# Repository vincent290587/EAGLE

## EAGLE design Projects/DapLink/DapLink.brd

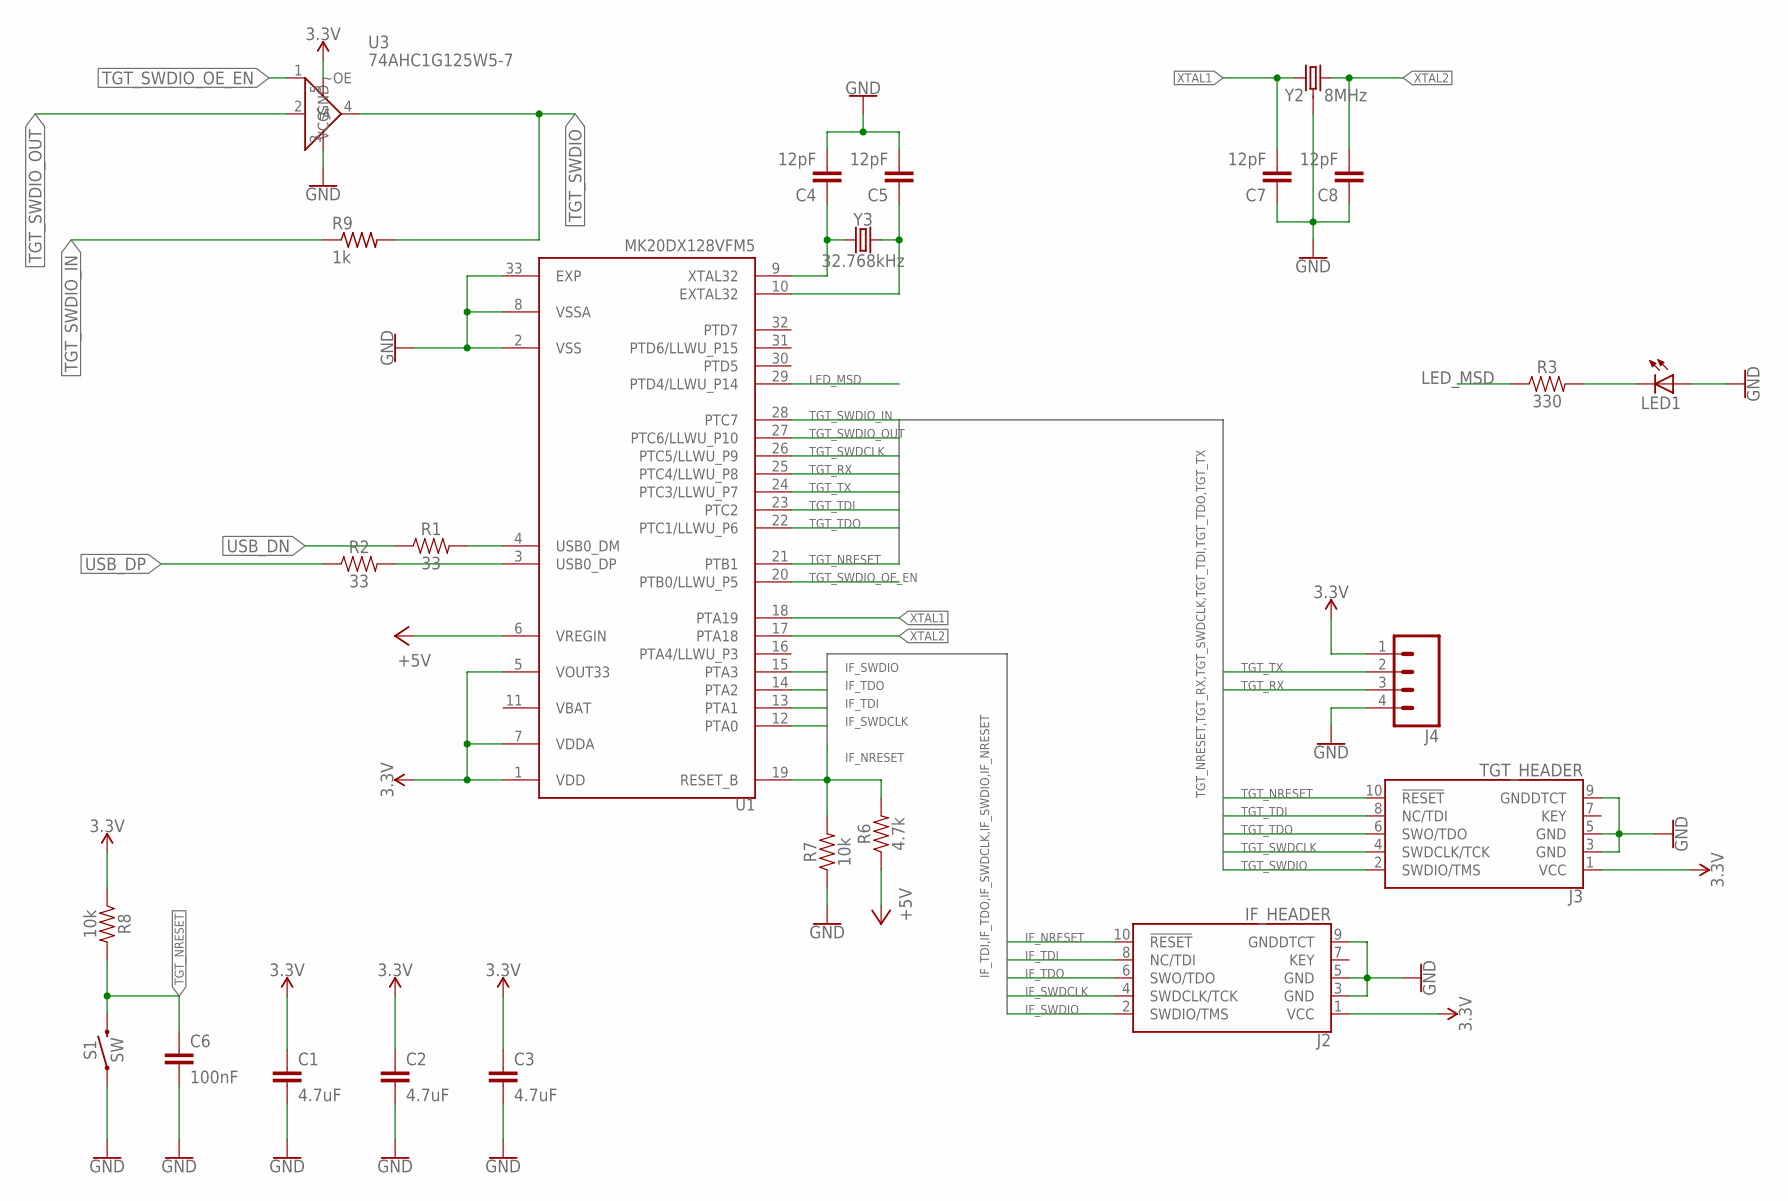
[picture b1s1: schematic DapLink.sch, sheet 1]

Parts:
C1, C2, C3: 4.7uF; 0603
C4, C5, C7, C8: 12pF; 0603
C6: 100nF; 0603
J2: IF_HEADER; 2X5-PTH-1.27MM
J3: TGT_HEADER; 2X5-PTH-1.27MM
J4: CONN_04; 1X04
LED1: LEDCHIP-LED0603; CHIP-LED0603
R1, R2: 33; 0603
R3: 330; 0603
R6: 4.7k; 0603
R7, R8: 10k; 0603
R9: 1k; R0603
S1: SW; TACTILE_SWITCH_PTH_6.0MM_KIT
U1: MK20DX128VFM5; QFN50P500X500X100-33N
U3: 74AHC1G125W5-7; SOT95P280X140-5N
Y2: 8MHz; CRYSTAL-SMD-5X3.2-4PAD
Y3: 32.768kHz; CRYSTAL-SMD-3.2X1.5MM

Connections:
3.3V: C1.1, C2.1, C3.1, J2.1 (VCC), J3.1 (VCC), J4.1, R8.1, U1.1 (VDD), U1.5 (VOUT33), U1.7 (VDDA), U3.5 (VCC); also elsewhere on the board
+5V: R6.1, U1.6 (VREGIN); also elsewhere on the board
GND: C1.2, C2.2, C3.2, C4.2, C5.2, C6.2, C7.1, C8.1, J2.3 (GND), J2.5 (GND), J2.9 (GNDDTCT), J3.3 (GND), J3.5 (GND), J3.9 (GNDDTCT), J4.4, LED1.A, R7.1, S1.1, U1.2 (VSS), U1.8 (VSSA), U1.33 (EXP), U3.3 (GND), Y2.2 (3), Y2.4 (3); also elsewhere on the board
IF_NRESET: J2.10 (!RESET), R6.2, R7.2, U1.19 (RESET_B)
IF_SWDCLK: J2.4 (SWDCLK/TCK), U1.12 (PTA0)
IF_SWDIO: J2.2 (SWDIO/TMS), U1.15 (PTA3)
IF_TDI: J2.8 (NC/TDI), U1.13 (PTA1)
IF_TDO: J2.6 (SWO/TDO), U1.14 (PTA2)
LED_MSD: R3.1, U1.29 (PTD4/LLWU_P14)
unnamed: C4.1, U1.9 (XTAL32), Y3.P$1 (1)
unnamed: C5.1, U1.10 (EXTAL32), Y3.P$2 (2)
unnamed: LED1.C, R3.2
TGT_NRESET: C6.1, J3.10 (!RESET), R8.2, S1.3 (2), U1.21 (PTB1)
TGT_RX: J4.3, U1.25 (PTC4/LLWU_P8)
TGT_SWDCLK: J3.4 (SWDCLK/TCK), U1.26 (PTC5/LLWU_P9)
TGT_SWDIO: J3.2 (SWDIO/TMS), R9.2, U3.4 (Y)
TGT_SWDIO_IN: R9.1, U1.28 (PTC7)
TGT_SWDIO_OE_EN: U1.20 (PTB0/LLWU_P5), U3.1 (~OE)
TGT_SWDIO_OUT: U1.27 (PTC6/LLWU_P10), U3.2 (A)
TGT_TDI: J3.8 (NC/TDI), U1.23 (PTC2)
TGT_TDO: J3.6 (SWO/TDO), U1.22 (PTC1/LLWU_P6)
TGT_TX: J4.2, U1.24 (PTC3/LLWU_P7)
USB0_DN: R1.2, U1.4 (USB0_DM)
USB0_DP: R2.2, U1.3 (USB0_DP)
USB_DN: R1.1; also elsewhere on the board
USB_DP: R2.1; also elsewhere on the board
VBAT: U1.11 (VBAT)
XTAL1: C7.2, U1.18 (PTA19), Y2.3 (1)
XTAL2: C8.2, U1.17 (PTA18), Y2.1 (2)

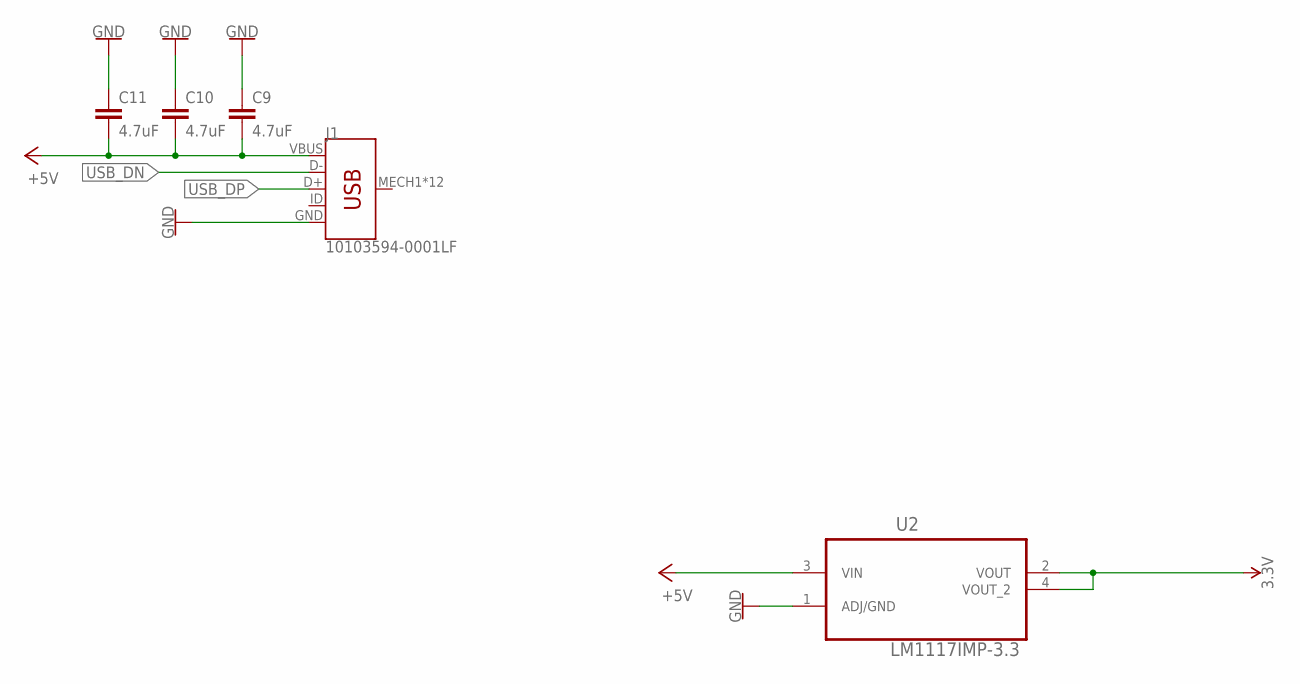
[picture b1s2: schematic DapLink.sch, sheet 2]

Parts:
C9, C10, C11: 4.7uF; C0603
J1: 10103594-0001LF
U2: LM1117IMP-3.3; SOT230P696X180-4N

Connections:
3.3V: U2.2 (VOUT), U2.4 (VOUT_2); also elsewhere on the board
+5V: C9.2, C10.2, C11.2, J1.VBUS, U2.3 (VIN); also elsewhere on the board
GND: C9.1, C10.1, C11.1, J1.GND, U2.1 (ADJ/GND); also elsewhere on the board
USB_DN: J1.D-; also elsewhere on the board
USB_DP: J1.D+; also elsewhere on the board

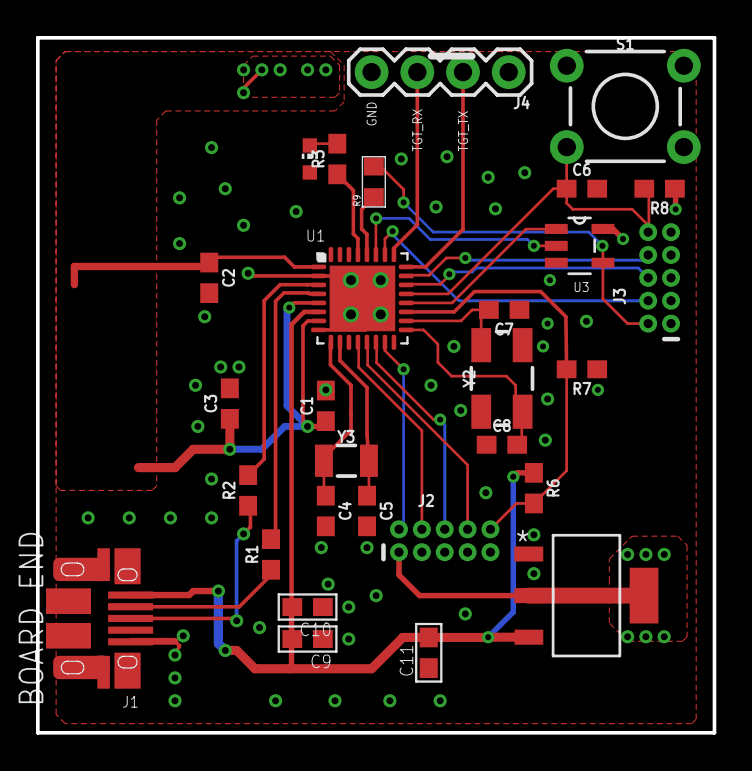
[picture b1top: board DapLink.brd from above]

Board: 2 copper layers, 37.6 x 38.6 mm, 29 parts (0 on the bottom side), 28 nets.

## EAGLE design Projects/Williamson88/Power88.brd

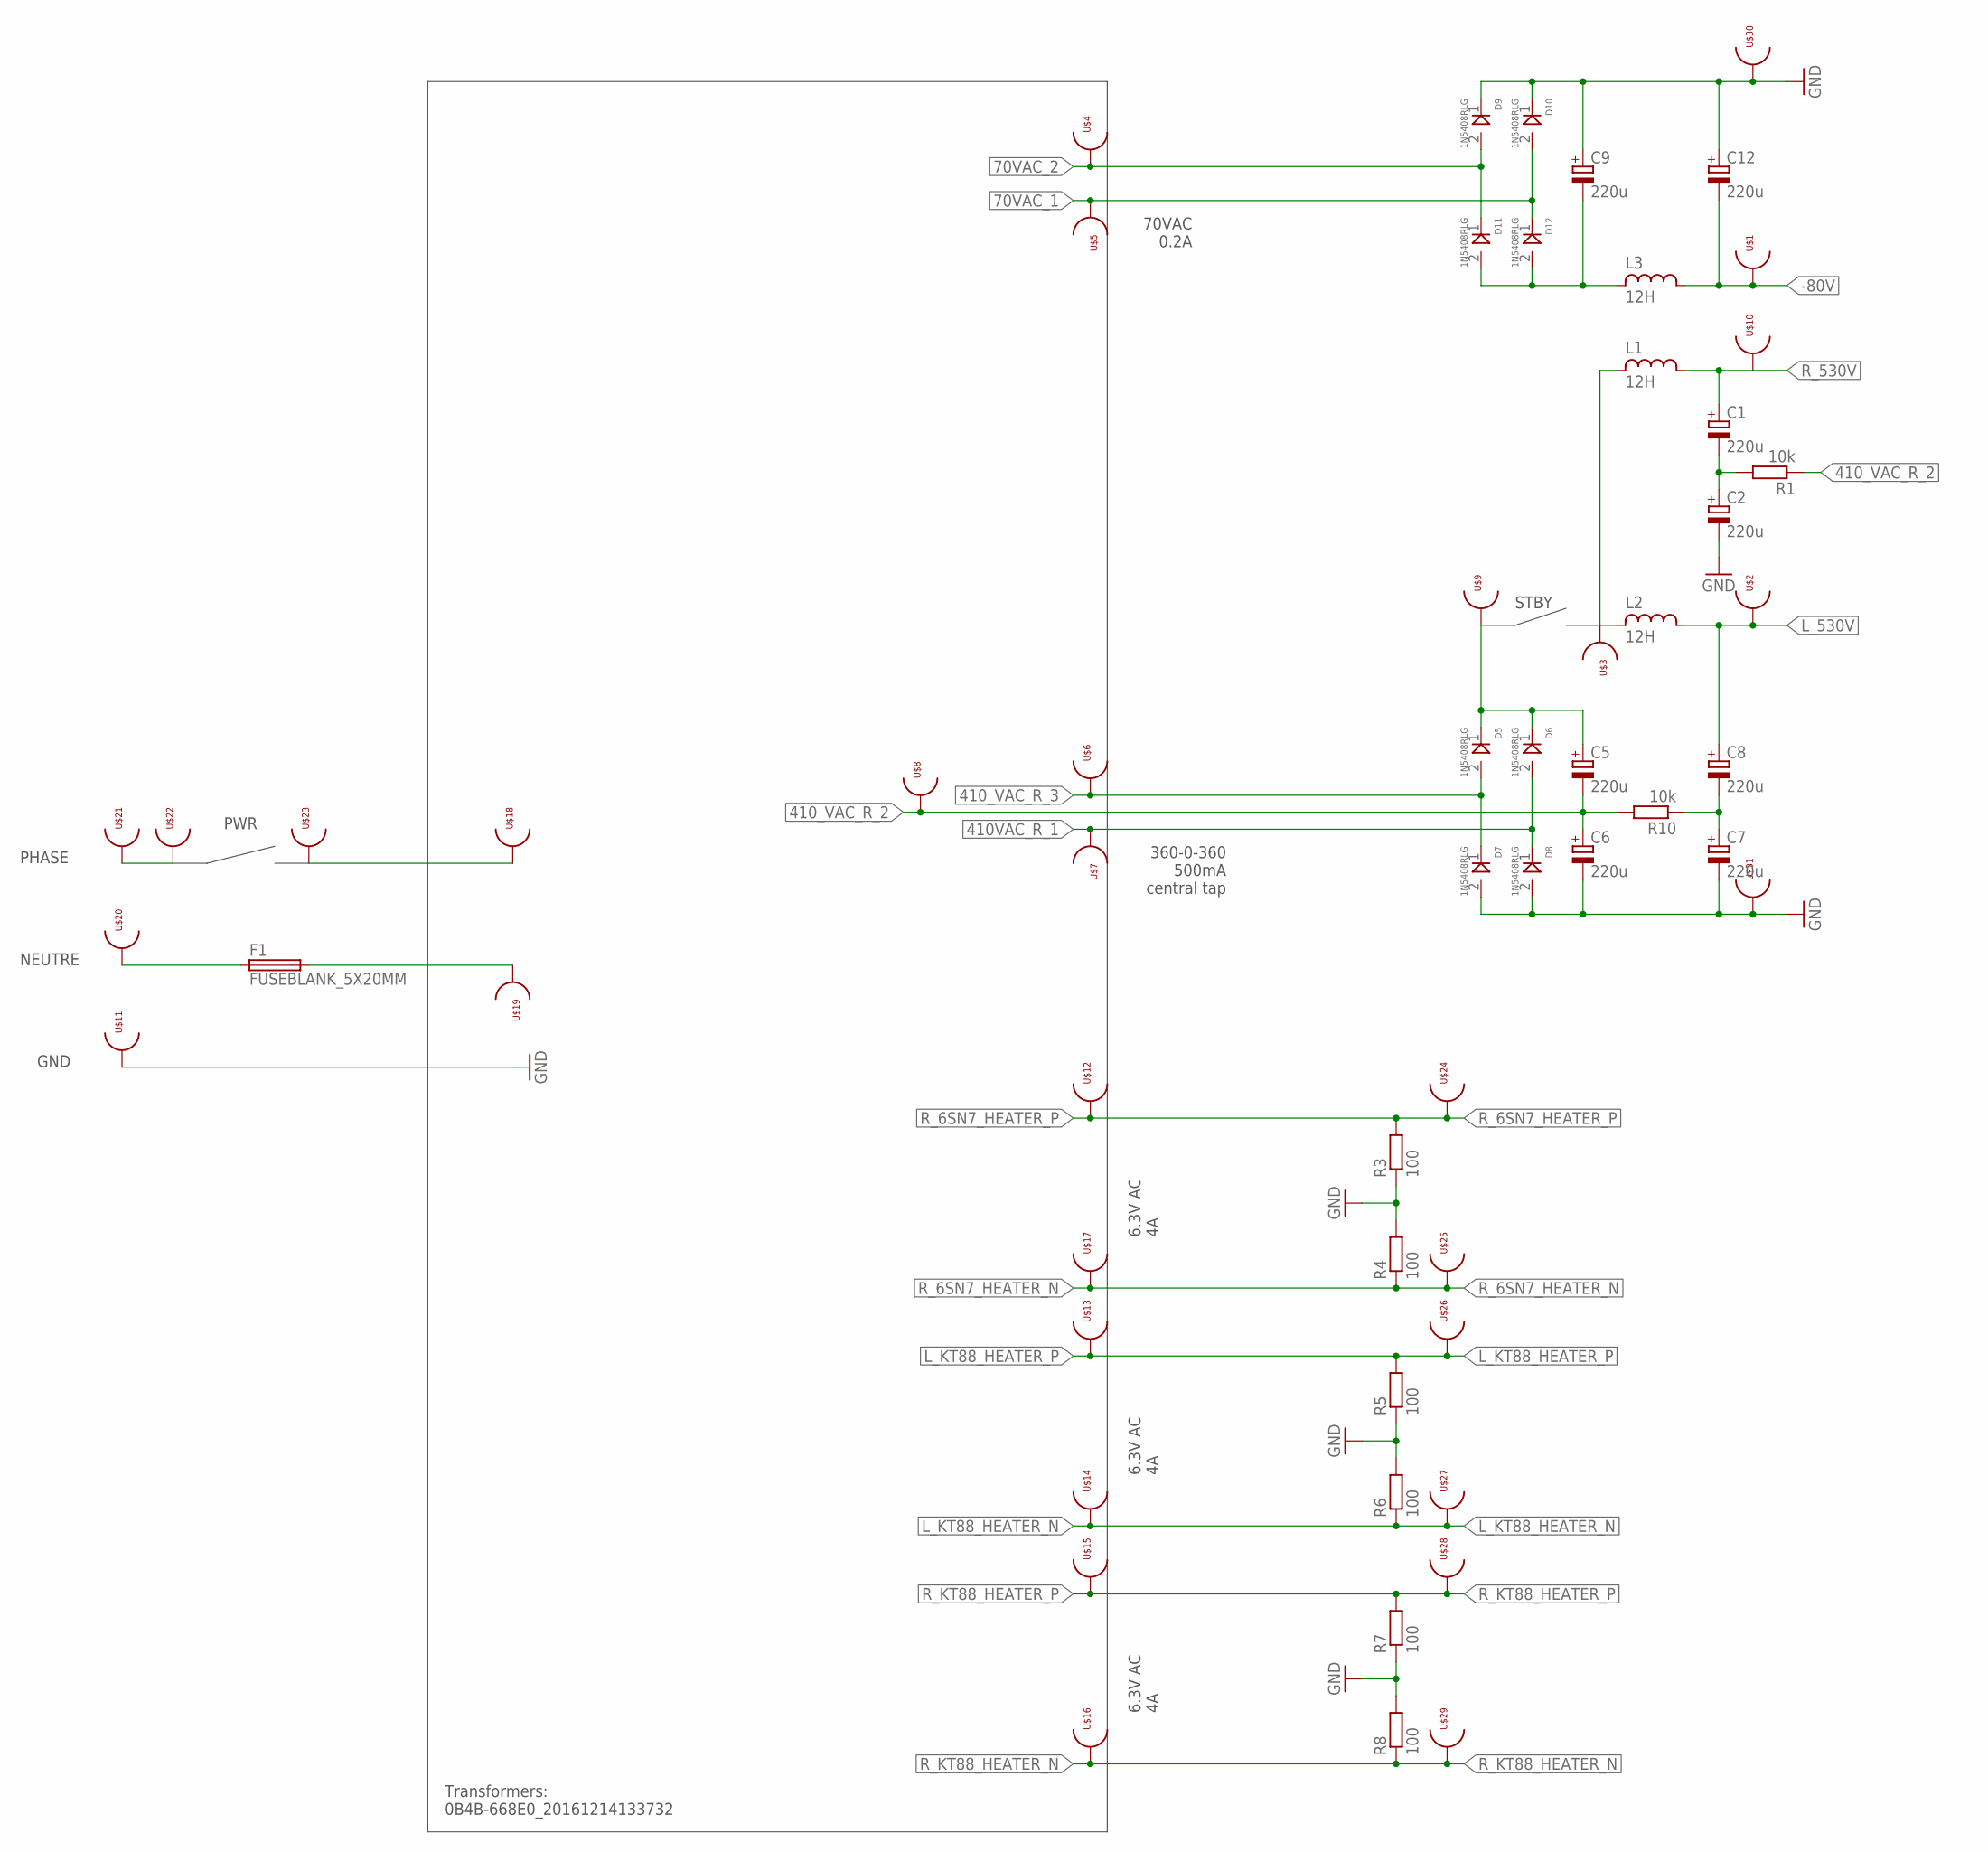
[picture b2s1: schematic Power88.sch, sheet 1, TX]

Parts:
C1, C2, C5, C6, C7, C8, C9, C12: 220u; E7,5-16; RATING 300V
D5, D6, D7, D8, D9, D10, D11, D12: 1N5408RLG; DIOAD2860W130L840D505
F1: FUSEBLANK_5X20MM; FUSE_HOLDER_5X20MM
L1, L2, L3: 12H; RL622; RATING 200mA
R1, R10: 10k; R1206
R3, R4, R5, R6, R7, R8: 100; R1206
U$1, U$2, U$3, U$4, U$5, U$6, U$7, U$8, U$9, U$10, U$11, U$12, U$13, U$14, U$15, U$16, U$17, U$18, U$19, U$20, U$21, U$22, U$23, U$24, U$25, U$26, U$27, U$28, U$29, U$30, U$31: TESTPOINT_HOLE; TESTPOINT_PHOLE

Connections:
70VAC_1: D10.2 (A), D12.1 (K), U$5.P$1
70VAC_2: D9.2 (A), D11.1 (K), U$4.P$1
410VAC_R_1: D6.2 (A), D8.1 (K), U$7.P$1
410_VAC_R_2: C5.-, C6.+, R1.1, R10.2, U$8.P$1
410_VAC_R_3: D5.2 (A), D7.1 (K), U$6.P$1
530V: C5.+, D5.1 (K), D6.1 (K), U$9.P$1
-80V: C12.-, L3.2, U$1.P$1
AC_PLUG_N: F1.1, U$20.P$1
AC_PLUG_PHASE: U$21.P$1, U$22.P$1
GND: C2.-, C6.-, C7.-, C9.+, C12.+, D7.2 (A), D8.2 (A), D9.1 (K), D10.1 (K), R3.1, R4.2, R5.1, R6.2, R7.1, R8.2, U$11.P$1, U$30.P$1, U$31.P$1
L_530V: C8.+, L2.2, U$2.P$1
L_KT88_HEATER_N: R6.1, U$14.P$1, U$27.P$1
L_KT88_HEATER_P: R5.2, U$13.P$1, U$26.P$1
unnamed: C7.+, C8.-, R10.1
unnamed: L1.1, L2.1, U$3.P$1
unnamed: C1.-, C2.+, R1.2
unnamed: F1.2, U$19.P$1
unnamed: C9.-, D11.2 (A), D12.2 (A), L3.1
R_6SN7_HEATER_N: R4.1, U$17.P$1, U$25.P$1
R_6SN7_HEATER_P: R3.2, U$12.P$1, U$24.P$1
R_530V: C1.+, L1.2, U$10.P$1
R_KT88_HEATER_N: R8.1, U$16.P$1, U$29.P$1
R_KT88_HEATER_P: R7.2, U$15.P$1, U$28.P$1
SW_ACIN: U$18.P$1, U$23.P$1

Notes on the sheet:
6.3V AC 4A
360-0-360 500mA central tap
70VAC 0.2A
Transformers: 0B4B-668E0_20161214133732
PWR
STBY
GND
NEUTRE
PHASE

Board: 2 copper layers, 59 parts (0 on the bottom side), 24 nets, no tracks yet.

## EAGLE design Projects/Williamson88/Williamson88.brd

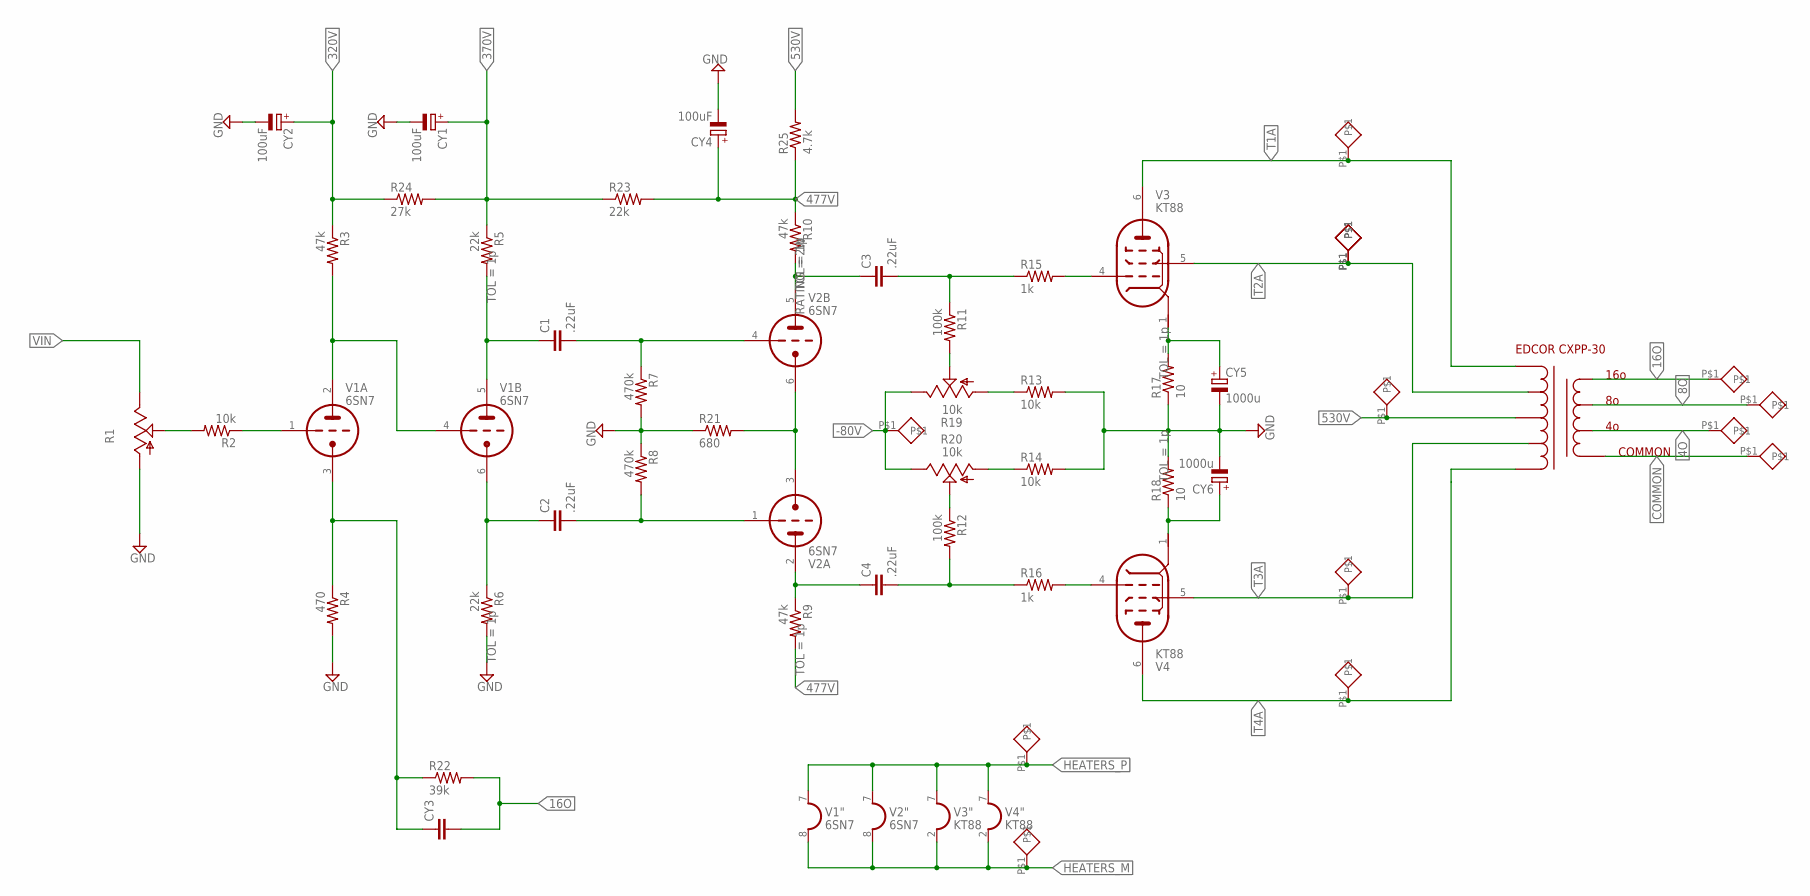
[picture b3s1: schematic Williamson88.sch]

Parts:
C1, C2, C3, C4: .22uF; C225-062X268; MPN 150224J630LE
CY1, CY2, CY4: 100uF; E7,5-18; RATING 600V
CY3: CYYC10B5; YC10B5
CY5, CY6: 1000u; E7,5-18; RATING 50V
R1: TRIM_US-B25P; B25P
R2, R13, R14: 10k; 0309/10
R3: 47k; 0309/10
R4: 470; 0309/10
R5, R6, R23: 22k; 0309/10
R7, R8: 470k; 0309/10
R9, R10: 47k; 0309/10; RATING 2W
R11, R12: 100k; 0309/10
R15, R16: 1k; 0309/10
R17, R18: 10; 0309/10; RATING 5W
R19, R20: 10k; B25P
R21: 680; 0309/10
R22: 39k; 0309/10
R24: 27k; 0309/10
R25: 4.7k; 0309/10; RATING 5W
U$1: CXPP30
U$2, U$3, U$4, U$5, U$6, U$7, U$8, U$9, U$10, U$14, U$15, U$17, U$18: W_CONN; WIRE_T
V1, V2: 6SN7; OKTAL
V3, V4: KT88; OKTAL

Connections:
4O: U$8.P$1
8O: U$7.P$1
16O: CY3.2, R22.2, U$6.P$1
320V: CY2.+, R3.1, R24.1
370V: CY1.+, R5.1, R23.1, R24.2
477V: CY4.+, R9.2, R10.1, R23.2, R25.1
530V: R25.2, U$18.P$1
-80V: R19.E, R20.E, U$10.P$1
COMMON: U$9.P$1
GND: CY1.-, CY2.-, CY4.-, CY5.-, CY6.-, R1.A, R4.2, R6.2, R7.2, R8.1, R13.2, R14.2, R17.1, R18.2, R21.1
HEATERS_M: U$15.P$1, V1.8 (H2), V2.8 (H2), V3.2 (H2), V4.2 (H2)
HEATERS_P: U$14.P$1, V1.7 (H1), V2.7 (H1), V3.7 (H1), V4.7 (H1)
unnamed: R3.2, V1.2 (TA), V1.4 (TG)
unnamed: CY3.1, R4.1, R22.1, V1.3 (TK)
unnamed: C2.1, R6.1, V1.6 (TK)
unnamed: C1.1, R5.2, V1.5 (TA)
unnamed: C1.2, R7.1, V2.4 (TG)
unnamed: C2.2, R8.2, V2.1 (TG)
unnamed: R1.S, R2.2
unnamed: R21.2, V2.3 (TK), V2.6 (TK)
unnamed: C3.1, R10.2, V2.5 (TA)
unnamed: C4.1, R9.1, V2.2 (TA)
unnamed: C3.2, R11.1, R15.1
unnamed: R15.2, V3.4 (PG)
unnamed: C4.2, R12.2, R16.1
unnamed: R16.2, V4.4 (PG)
unnamed: CY5.+, R17.2, V3.1 (PK)
unnamed: CY6.+, R18.1, V4.1 (PK)
unnamed: R13.1, R19.A
unnamed: R2.1, V1.1 (TG)
unnamed: R14.1, R20.A
unnamed: R12.1, R20.S
unnamed: R11.2, R19.S
T1A: U$2.P$1, V3.6 (PA)
T2A: U$3.P$1, U$17.P$1, V3.5 (PSG)
T3A: U$4.P$1, V4.5 (PSG)
T4A: U$5.P$1, V4.6 (PA)
VIN: R1.E

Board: 2 copper layers, 53 parts (0 on the bottom side), 34 nets, no tracks yet.

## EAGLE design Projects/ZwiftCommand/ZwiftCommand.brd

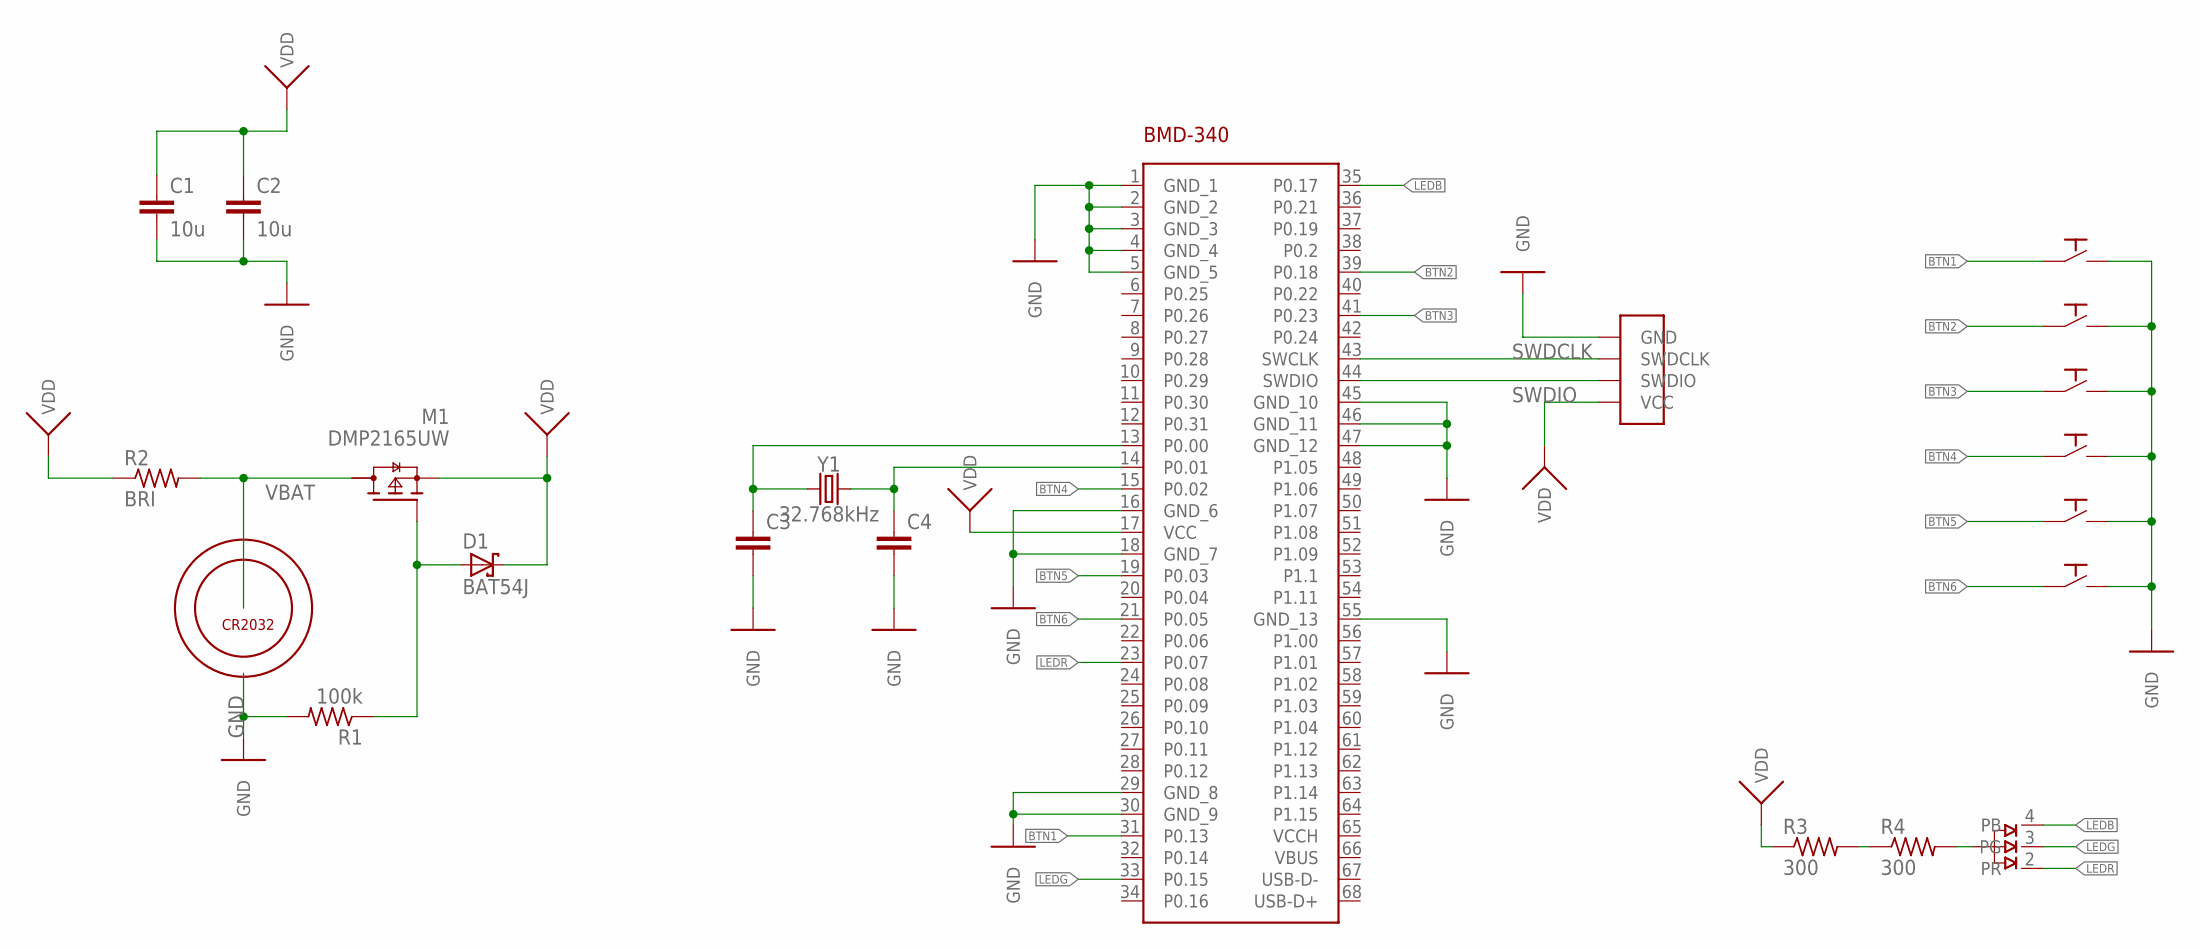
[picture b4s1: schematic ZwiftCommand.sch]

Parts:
C1, C2: 10u; C0603
C3, C4: C-EUC0603; C0603
D1: BAT54J; SOD323(F)
D2: LRTBR48G; LRTBR48GP9Q71R7S526NP68
IC1: BMD-340-A-R; BMD340AR
M1: DMP2165UW; SOT65P210X110-3N
R1: 100k; R0603
R2: BRI; R0402
R3, R4: 300; R0603
SPST1, SPST2, SPST3, SPST4, SPST5, SPST6: PTS526SK08; PTS526SKG15SMTR2LFS
U1: BAT-HLD-001-THM; BATHLD001THM
U$2: PROG_SMD
Y1: 32.768kHz; CRYSTAL-SMD-3.2X1.5MM

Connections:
BTN1: IC1.31 (P0.13), SPST1.1, SPST1.2
BTN2: IC1.39 (P0.18), SPST2.1, SPST2.2
BTN3: IC1.41 (P0.23), SPST3.1, SPST3.2
BTN4: IC1.15 (P0.02), SPST4.1, SPST4.2
BTN5: IC1.19 (P0.03), SPST5.1, SPST5.2
BTN6: IC1.21 (P0.05), SPST6.1, SPST6.2
GND: C1.2, C2.2, C3.2, C4.2, IC1.1 (GND_1), IC1.2 (GND_2), IC1.3 (GND_3), IC1.4 (GND_4), IC1.5 (GND_5), IC1.16 (GND_6), IC1.18 (GND_7), IC1.29 (GND_8), IC1.30 (GND_9), IC1.45 (GND_10), IC1.46 (GND_11), IC1.47 (GND_12), IC1.55 (GND_13), R1.2, SPST1.3, SPST1.4, SPST2.3, SPST2.4, SPST3.3, SPST3.4, SPST4.3, SPST4.4, SPST5.3, SPST5.4, SPST6.3, SPST6.4, U1.5 (-), U$2.GND
LEDB: D2.4 (PB), IC1.35 (P0.17)
LEDG: D2.3 (PG), IC1.33 (P0.15)
LEDR: D2.2 (PR), IC1.23 (P0.07)
unnamed: C3.1, IC1.13 (P0.00), Y1.P$1 (1)
unnamed: D1.2 (A), M1.1 (G), R1.1
unnamed: R3.2, R4.1
unnamed: C4.1, IC1.14 (P0.01), Y1.P$2 (2)
unnamed: D2.1, R4.2
SWDCLK: IC1.43 (SWCLK), U$2.PIN1 (SWDCLK)
SWDIO: IC1.44 (SWDIO), U$2.PIN2 (SWDIO)
VBAT: M1.3 (D), R2.2, U1.1 (+), U1.2 (+), U1.3 (+), U1.4 (+)
VDD: C1.1, C2.1, D1.1 (K), IC1.17 (VCC), M1.2 (S), R2.1, R3.1, U$2.VCC

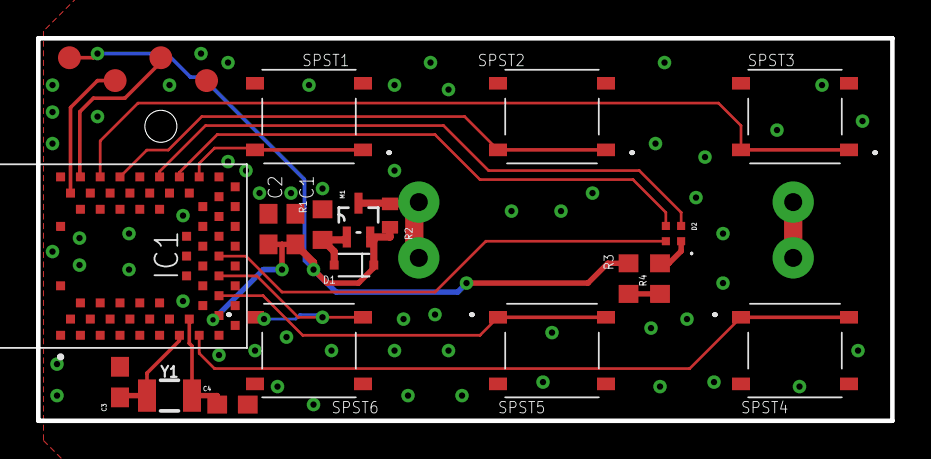
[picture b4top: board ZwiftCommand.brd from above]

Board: 2 copper layers, 47.4 x 21.2 mm, 21 parts (1 on the bottom side), 19 nets.

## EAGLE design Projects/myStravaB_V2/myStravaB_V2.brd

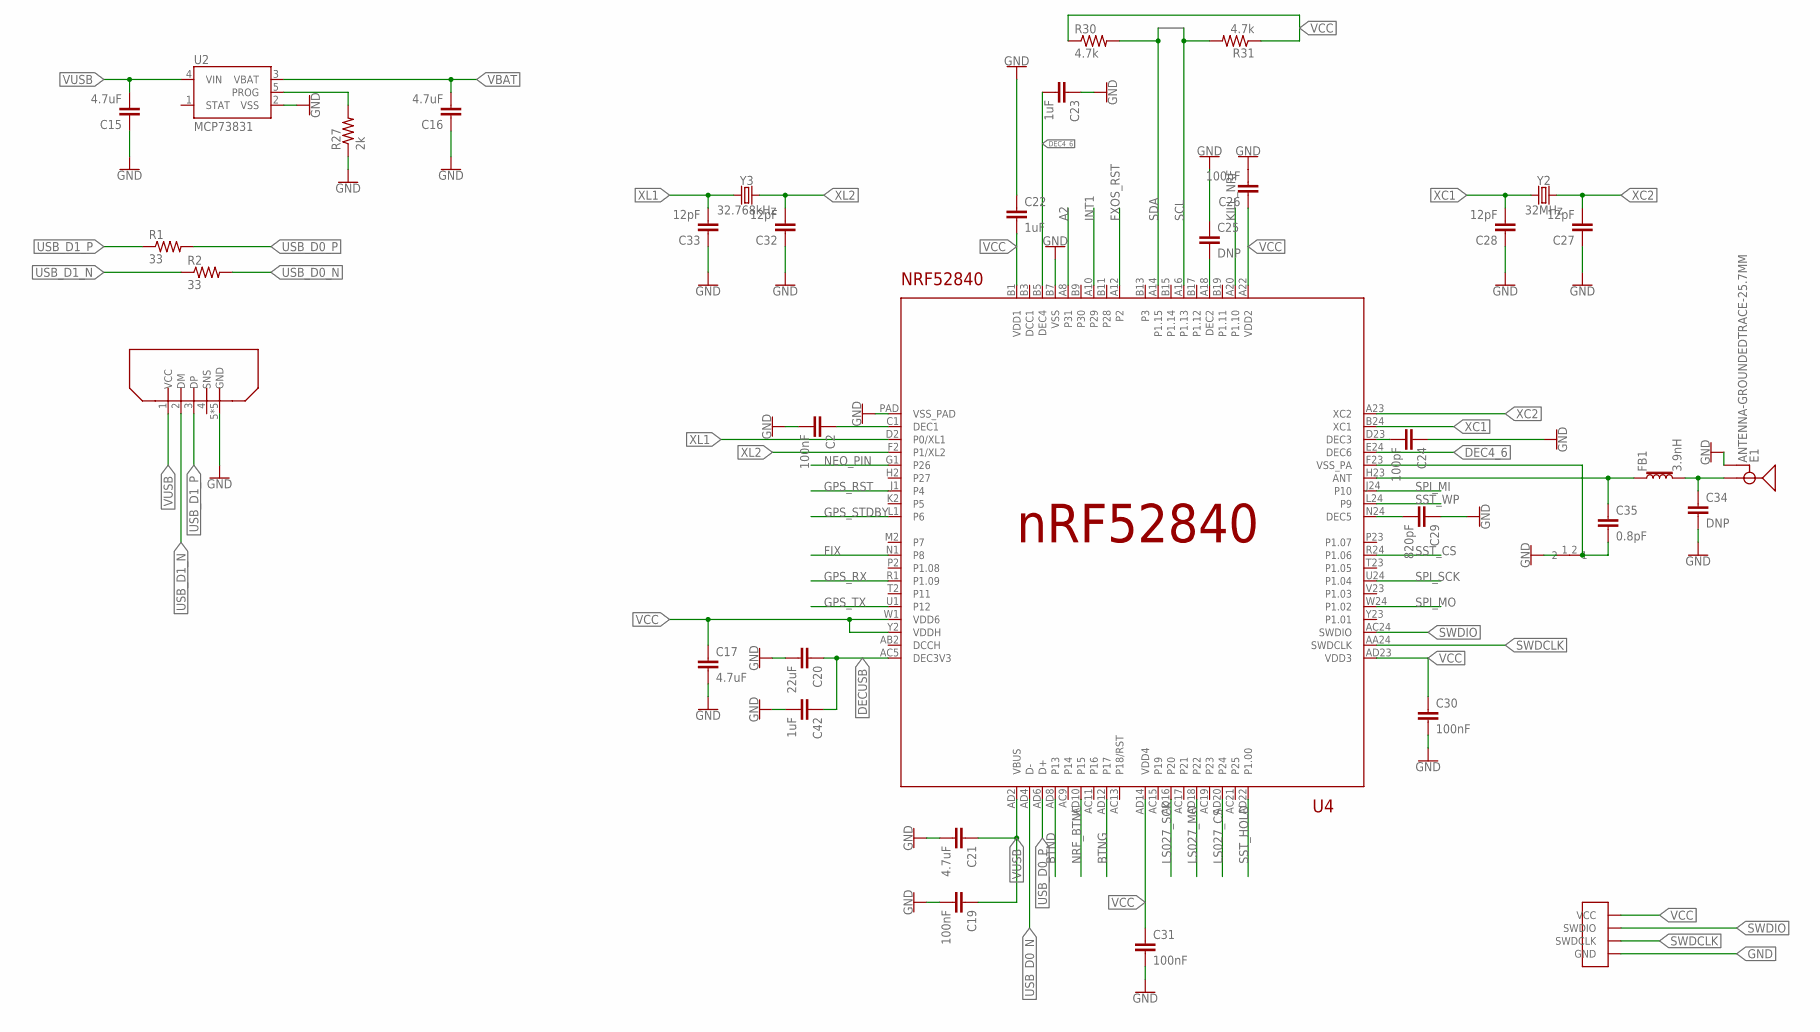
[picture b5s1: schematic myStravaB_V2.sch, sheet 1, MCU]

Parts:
C2, C19, C26: 100nF; C0603
C15, C16, C21: 4.7uF; C0805
C17: 4.7uF; C0603
C20: 22uF; C0603
C22, C23: 1uF; 0603
C24: 100pF; C0603
C25: DNP; C0402
C27, C28: 12pF; C0402
C29: 820pF; C0603
C30, C31: 100nF; C0402
C32, C33: 12pF; C0603
C34: DNP; 0603
C35: 0.8pF; C0402
C42: 1uF; C0603
E1: ANTENNA-GROUNDEDTRACE-25.7MM; TRACE_ANTENNA_2.4GHZ_25.7MM
FB1: 3.9nH; 0603
R1, R2: 33; R0603
R27: 2k; R0603
R30, R31: 4.7k; R0603
U2: MCP73831; SOT23-5
U4: NRF52840; AQFN73
U$3: ZX80B5P
U$7: PROG_SMD
U$8: NET_CONN
Y2: 32MHz; CRYSTAL-SMD-5X3.2-4PAD
Y3: 32.768kHz; CRYSTAL-SMD-3.2X1.5MM

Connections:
A2: U4.A8 (P31)
BTND: U4.AD8 (P13); also elsewhere on the board
BTNG: U4.AD12 (P17); also elsewhere on the board
DEC1: C2.1, U4.C1 (DEC1)
DEC2: C25.2, U4.A18 (DEC2)
DEC3: C24.2, U4.D23 (DEC3)
DEC4_6: C23.2, U4.B5 (DEC4), U4.E24 (DEC6)
DEC5: C29.2, U4.N24 (DEC5)
DECUSB: C20.1, C42.1, U4.AC5 (DEC3V3)
FIX: U4.N1 (P8); also elsewhere on the board
FXOS_RST: U4.A12 (P2); also elsewhere on the board
GND: C2.2, C15.1, C16.1, C17.2, C19.2, C20.2, C21.2, C22.1, C23.1, C24.1, C25.1, C26.2, C27.1, C28.1, C29.1, C30.2, C31.2, C32.1, C33.1, C34.2, C42.2, E1.GND, E1.GND2 (GND), R27.1, U2.2 (VSS), U4.B7 (VSS), U4.PAD (VSS_PAD), U$3.5 (GND), U$3.GND1 (GND), U$3.GND2 (GND), U$3.GND3 (GND), U$3.GND4 (GND), U$7.GND, U$8.1; also elsewhere on the board
GPS_RST: U4.J1 (P4); also elsewhere on the board
GPS_RX: U4.R1 (P1.09); also elsewhere on the board
GPS_STDBY: U4.L1 (P6); also elsewhere on the board
GPS_TX: U4.U1 (P12); also elsewhere on the board
INT1: U4.A10 (P29); also elsewhere on the board
KILL_NRF: U4.A20 (P1.10); also elsewhere on the board
LS027_CS: U4.AD20 (P24); also elsewhere on the board
LS027_MO: U4.AD18 (P22); also elsewhere on the board
LS027_SCK: U4.AD16 (P20); also elsewhere on the board
unnamed: C35.1, FB1.1, U4.H23 (ANT)
unnamed: C34.1, E1.ANT (SIGNAL), FB1.2
unnamed: C35.2, U4.F23 (VSS_PA), U$8.2
unnamed: R27.2, U2.5 (PROG)
NEO_PIN: U4.G1 (P26); also elsewhere on the board
NRF_BTNC: U4.AD10 (P15); also elsewhere on the board
SCL: R31.2, U4.A16 (P1.13); also elsewhere on the board
SDA: R30.2, U4.A14 (P1.15); also elsewhere on the board
SPI_MI: U4.J24 (P10); also elsewhere on the board
SPI_MO: U4.W24 (P1.02); also elsewhere on the board
SPI_SCK: U4.U24 (P1.04); also elsewhere on the board
SST_CS: U4.R24 (P1.06); also elsewhere on the board
SST_HOLD: U4.AD22 (P1.00); also elsewhere on the board
SST_WP: U4.L24 (P9); also elsewhere on the board
SWDCLK: U4.AA24 (SWDCLK), U$7.PIN1 (SWDCLK)
SWDIO: U4.AC24 (SWDIO), U$7.PIN2 (SWDIO)
USB_D0_N: R2.2, U4.AD4 (D-)
USB_D0_P: R1.2, U4.AD6 (D+)
USB_D1_N: R2.1, U$3.2 (DM)
USB_D1_P: R1.1, U$3.3 (DP)
VBAT: C16.2, U2.3 (VBAT); also elsewhere on the board
VCC: C17.1, C22.2, C26.1, C30.1, C31.1, R30.1, R31.1, U4.A22 (VDD2), U4.AD14 (VDD4), U4.AD23 (VDD3), U4.B1 (VDD1), U4.W1 (VDD6), U4.Y2 (VDDH), U$7.VCC; also elsewhere on the board
VUSB: C15.2, C19.1, C21.1, U2.4 (VIN), U4.AD2 (VBUS), U$3.1 (VCC); also elsewhere on the board
XC1: C28.2, U4.B24 (XC1), Y2.1
XC2: C27.2, U4.A23 (XC2), Y2.3 (2)
XL1: C33.2, U4.D2 (P0/XL1), Y3.P$1 (1)
XL2: C32.2, U4.F2 (P1/XL2), Y3.P$2 (2)

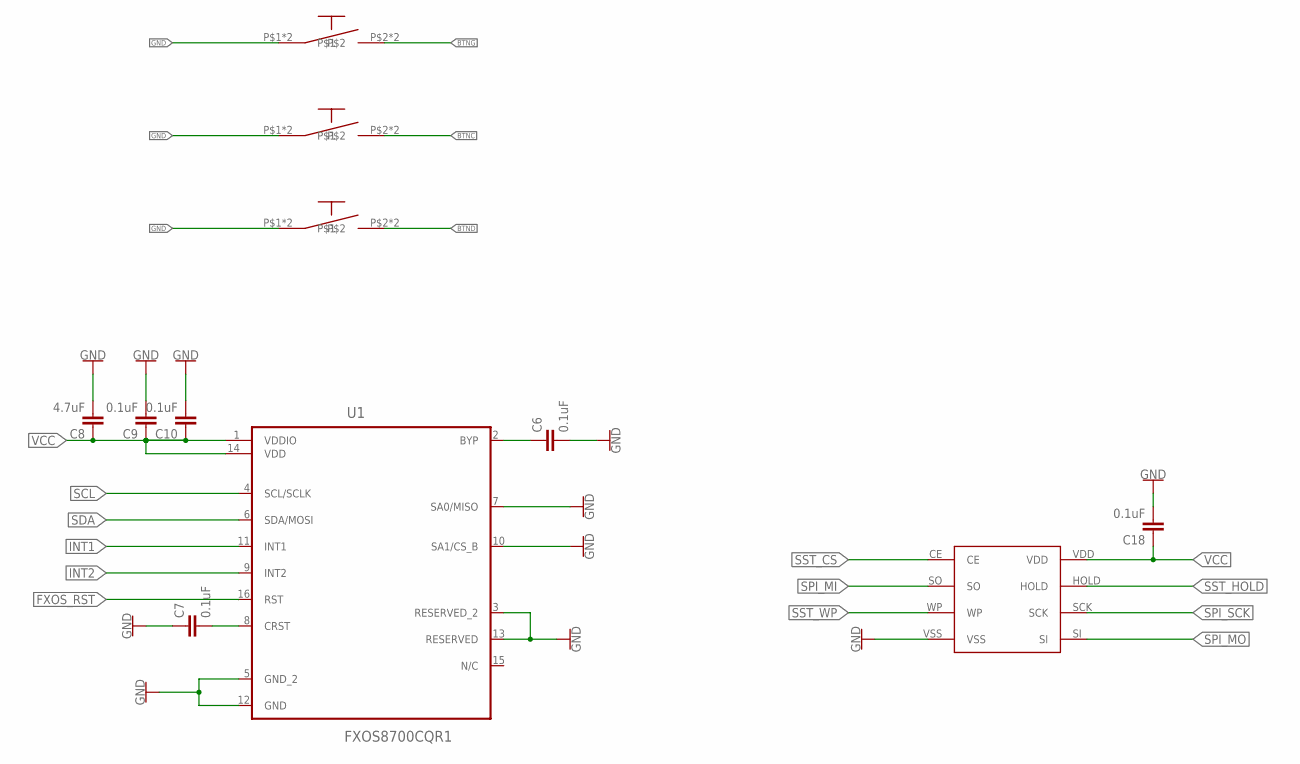
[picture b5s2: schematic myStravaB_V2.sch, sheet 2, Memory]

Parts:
BTNC1: SKRMAAE010
BTND1: SKRMAAE010
BTNG1: SKRMAAE010
C6, C7, C9, C10, C18: 0.1uF; 0603
C8: 4.7uF; 0603
U1: FXOS8700CQR1; QFN50P300X300X120-16N
U$2: FLASH; SOIC8

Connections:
BTNC: BTNC1.P$2, BTNC1.P$4; also elsewhere on the board
BTND: BTND1.P$2, BTND1.P$4; also elsewhere on the board
BTNG: BTNG1.P$2, BTNG1.P$4; also elsewhere on the board
BYP: C6.1, U1.2 (BYP)
CRST: C7.2, U1.8 (CRST)
FXOS_RST: U1.16 (RST); also elsewhere on the board
GND: BTNC1.P$1, BTNC1.P$3, BTND1.P$1, BTND1.P$3, BTNG1.P$1, BTNG1.P$3, C6.2, C7.1, C8.2, C9.2, C10.2, C18.2, U1.3 (RESERVED_2), U1.5 (GND_2), U1.7 (SA0/MISO), U1.10 (SA1/CS_B), U1.12 (GND), U1.13 (RESERVED), U$2.VSS; also elsewhere on the board
INT1: U1.11 (INT1); also elsewhere on the board
INT2: U1.9 (INT2)
SCL: U1.4 (SCL/SCLK); also elsewhere on the board
SDA: U1.6 (SDA/MOSI); also elsewhere on the board
SPI_MI: U$2.SO; also elsewhere on the board
SPI_MO: U$2.SI; also elsewhere on the board
SPI_SCK: U$2.SCK; also elsewhere on the board
SST_CS: U$2.CE; also elsewhere on the board
SST_HOLD: U$2.HOLD; also elsewhere on the board
SST_WP: U$2.WP; also elsewhere on the board
VCC: C8.1, C9.1, C10.1, C18.1, U1.1 (VDDIO), U1.14 (VDD), U$2.VDD; also elsewhere on the board

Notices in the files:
parts and their libraries:
Sparkfun-clocks: Licensing: Creative Commons ShareAlike 4.0 International - https://creativecommons.org/licenses/by-sa/4.0
inductor-bourns: Copyright (C) 2008, Bob Starr
